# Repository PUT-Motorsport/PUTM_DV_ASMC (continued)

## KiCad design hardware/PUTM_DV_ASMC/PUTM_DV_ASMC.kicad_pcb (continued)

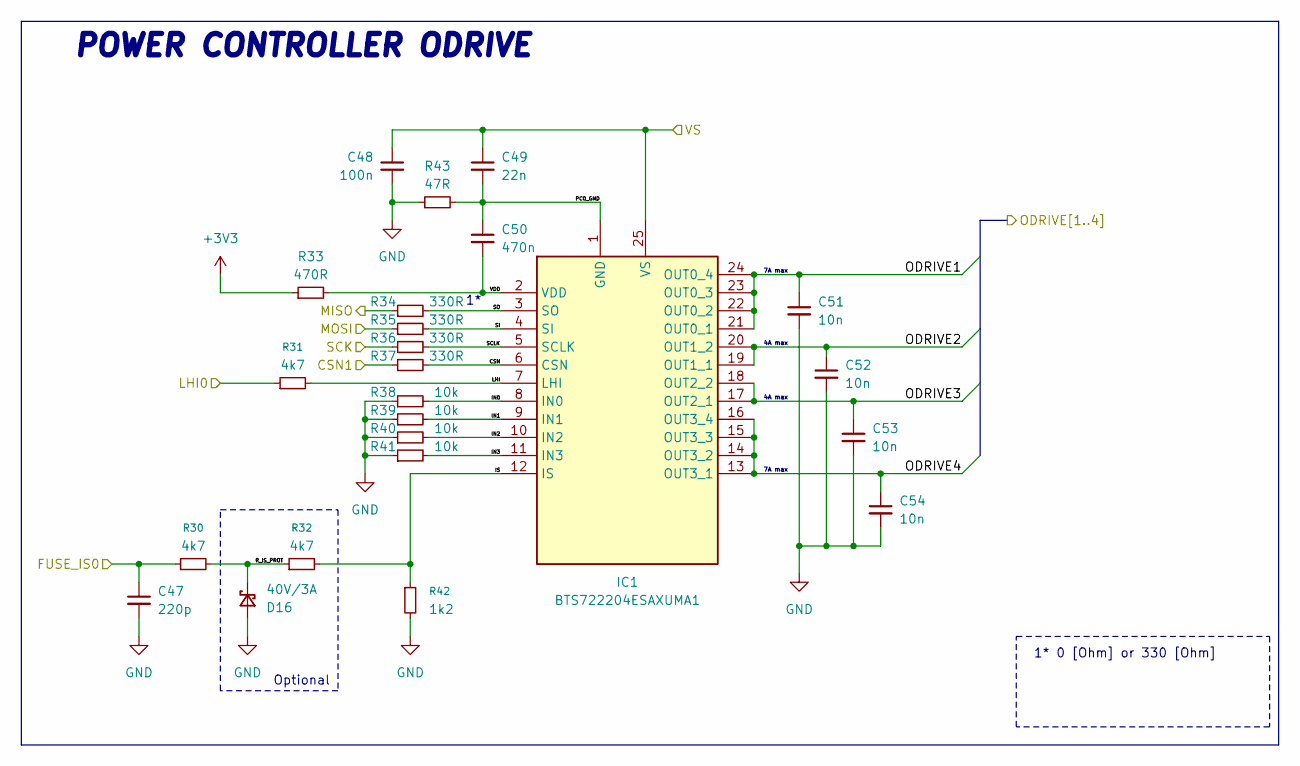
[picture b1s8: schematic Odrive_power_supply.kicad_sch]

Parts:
C47: 220p; C_0603_1608Metric_Pad1.08x0.95mm_HandSolder; Mouser Part Number 81-GCM1885C1H221JA6J
C48: 100n; C_0603_1608Metric_Pad1.08x0.95mm_HandSolder; Mouser Part Number 81-GCJ188R71H104KA2D
C49: 22n; C_0603_1608Metric_Pad1.08x0.95mm_HandSolder; Mouser Part Number GCE188R71H223KA01D
C50: 470n; C_0603_1608Metric_Pad1.08x0.95mm_HandSolder; Mouser Part Number 810-C1608X7R1H474K0E
C51, C52, C53, C54: 10n; C_0603_1608Metric_Pad1.08x0.95mm_HandSolder; Mouser Part Number 81-GCE188R71H103KA1D
D16: 40V/3A; D_SOD-123F; Mouser Part Number 637-SKL34
IC1: BTS722204ESAXUMA1; SOP65P600X115-25N; Mouser Part Number 726-BTS722204ESAXUMA
R30, R31, R32: 4k7; R_0603_1608Metric_Pad0.98x0.95mm_HandSolder; Mouser Part Number 71-CRCW0603-4.7K-E3
R33: 470R; R_0603_1608Metric_Pad0.98x0.95mm_HandSolder; Mouser Part Number 71-CRCW0603J-470-E3
R34, R35, R36, R37: 330R; R_0603_1608Metric_Pad0.98x0.95mm_HandSolder; Mouser Part Number 71-CRCW0603-330-E3
R38, R39, R40, R41: 10k; R_0603_1608Metric_Pad0.98x0.95mm_HandSolder; Mouser Part Number 71-CRCW060310K0FKEAH
R42: 1k2; R_0603_1608Metric_Pad0.98x0.95mm_HandSolder; Mouser Part Number 71-CRCW0603-1.2K-E3
R43: 47R; R_0603_1608Metric_Pad0.98x0.95mm_HandSolder; Mouser Part Number 71-RCS060347R0JNEA

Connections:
+3V3: R33.1; also elsewhere on the board
+BATT: C48.1, C49.1, IC1.25 (VS); also elsewhere on the board
/Connectors/ODRIVE4: C51.1, C52.1, C53.1, C54.1, IC1.13 (OUT3_1), IC1.14 (OUT3_2), IC1.15 (OUT3_3), IC1.16 (OUT3_4), IC1.17 (OUT2_1), IC1.18 (OUT2_2), IC1.19 (OUT1_1), IC1.20 (OUT1_2), IC1.21 (OUT0_1), IC1.22 (OUT0_2), IC1.23 (OUT0_3), IC1.24 (OUT0_4); also elsewhere on the board
/DV_power_supply/FUSE_IS0: C47.1, R30.1; also elsewhere on the board
/DV_power_supply/LHI0: R31.1; also elsewhere on the board
/DV_power_supply/Odrive_power_supply/CSN: IC1.6 (CSN), R37.2
/DV_power_supply/Odrive_power_supply/IN0: IC1.8 (IN0), R38.2
/DV_power_supply/Odrive_power_supply/IN1: IC1.9 (IN1), R39.2
/DV_power_supply/Odrive_power_supply/IN2: IC1.10 (IN2), R40.2
/DV_power_supply/Odrive_power_supply/IN3: IC1.11 (IN3), R41.2
/DV_power_supply/Odrive_power_supply/IS: IC1.12 (IS), R32.2, R42.1
/DV_power_supply/Odrive_power_supply/LHI: IC1.7 (LHI), R31.2
/DV_power_supply/Odrive_power_supply/PC0_GND: C49.2, C50.1, IC1.1 (GND), R43.2
/DV_power_supply/Odrive_power_supply/R_IS_PROT: D16.1 (K), R30.2, R32.1
/DV_power_supply/Odrive_power_supply/SCLK: IC1.5 (SCLK), R36.2
/DV_power_supply/Odrive_power_supply/SI: IC1.4 (SI), R35.2
/DV_power_supply/Odrive_power_supply/SO: IC1.3 (SO), R34.2
/DV_power_supply/Odrive_power_supply/VDD: C50.2, IC1.2 (VDD), R33.2
/DV_power_supply/SPI1.CSN1: R37.1; also elsewhere on the board
/DV_power_supply/SPI1.MISO: R34.1; also elsewhere on the board
/DV_power_supply/SPI1.MOSI: R35.1; also elsewhere on the board
/DV_power_supply/SPI1.SCK: R36.1; also elsewhere on the board
GND: C47.2, C48.2, C51.2, C52.2, C53.2, C54.2, D16.2 (A), R38.1, R39.1, R40.1, R41.1, R42.2, R43.1; also elsewhere on the board

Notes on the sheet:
4A max
Optional
1* 0 [Ohm] or 330 [Ohm]
POWER CONTROLLER ODRIVE
7A max

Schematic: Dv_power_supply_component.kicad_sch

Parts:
C55: 220p; C_0603_1608Metric_Pad1.08x0.95mm_HandSolder; Mouser Part Number 81-GCM1885C1H221JA6J
C56: 100n; C_0603_1608Metric_Pad1.08x0.95mm_HandSolder; Mouser Part Number 81-GCJ188R71H104KA2D
C57: 22n; C_0603_1608Metric_Pad1.08x0.95mm_HandSolder; Mouser Part Number GCE188R71H223KA01D
C58: 470n; C_0603_1608Metric_Pad1.08x0.95mm_HandSolder; Mouser Part Number 810-C1608X7R1H474K0E
C59, C60, C61, C62: 10n; C_0603_1608Metric_Pad1.08x0.95mm_HandSolder; Mouser Part Number 81-GCE188R71H103KA1D
D17: 40V/3A; D_SOD-123F; Mouser Part Number 637-SKL34
IC2: BTS722204ESAXUMA1; SOP65P600X115-25N; Mouser Part Number 726-BTS722204ESAXUMA
R44, R45, R46: 4k7; R_0603_1608Metric_Pad0.98x0.95mm_HandSolder; Mouser Part Number 71-CRCW0603-4.7K-E3
R47: 470R; R_0603_1608Metric_Pad0.98x0.95mm_HandSolder; Mouser Part Number 71-CRCW0603J-470-E3
R48, R49, R50, R51: 330R; R_0603_1608Metric_Pad0.98x0.95mm_HandSolder; Mouser Part Number 71-CRCW0603-330-E3
R52, R53, R54, R55: 10k; R_0603_1608Metric_Pad0.98x0.95mm_HandSolder; Mouser Part Number 71-CRCW060310K0FKEAH
R56: 1k2; R_0603_1608Metric_Pad0.98x0.95mm_HandSolder; Mouser Part Number 71-CRCW0603-1.2K-E3
R57: 47R; R_0603_1608Metric_Pad0.98x0.95mm_HandSolder; Mouser Part Number 71-RCS060347R0JNEA

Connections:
+3V3: R47.1; also elsewhere on the board
+BATT: C56.1, C57.1, IC2.25 (VS); also elsewhere on the board
/Connectors/OUT_ASSI: C60.1, IC2.19 (OUT1_1), IC2.20 (OUT1_2); also elsewhere on the board
/Connectors/OUT_EBS: C61.1, IC2.17 (OUT2_1), IC2.18 (OUT2_2); also elsewhere on the board
/Connectors/OUT_LIDAR: C59.1, IC2.21 (OUT0_1), IC2.22 (OUT0_2), IC2.23 (OUT0_3), IC2.24 (OUT0_4); also elsewhere on the board
/Connectors/OUT_RES: C62.1, IC2.13 (OUT3_1), IC2.14 (OUT3_2), IC2.15 (OUT3_3), IC2.16 (OUT3_4); also elsewhere on the board
/DV_power_supply/Dv_power_supply_component/CSN: IC2.6 (CSN), R51.2
/DV_power_supply/Dv_power_supply_component/IN0: IC2.8 (IN0), R52.2
/DV_power_supply/Dv_power_supply_component/IN1: IC2.9 (IN1), R53.2
/DV_power_supply/Dv_power_supply_component/IN2: IC2.10 (IN2), R54.2
/DV_power_supply/Dv_power_supply_component/IN3: IC2.11 (IN3), R55.2
/DV_power_supply/Dv_power_supply_component/IS: IC2.12 (IS), R46.2, R56.1
/DV_power_supply/Dv_power_supply_component/LHI: IC2.7 (LHI), R45.2
/DV_power_supply/Dv_power_supply_component/PC0_GND: C57.2, C58.1, IC2.1 (GND), R57.2
/DV_power_supply/Dv_power_supply_component/R_IS_PROT: D17.1 (K), R44.2, R46.1
/DV_power_supply/Dv_power_supply_component/SCLK: IC2.5 (SCLK), R50.2
/DV_power_supply/Dv_power_supply_component/SI: IC2.4 (SI), R49.2
/DV_power_supply/Dv_power_supply_component/SO: IC2.3 (SO), R48.2
/DV_power_supply/Dv_power_supply_component/VDD: C58.2, IC2.2 (VDD), R47.2
/DV_power_supply/FUSE_IS1: C55.1, R44.1; also elsewhere on the board
/DV_power_supply/LHI1: R45.1; also elsewhere on the board
/DV_power_supply/SPI1.CSN2: R51.1; also elsewhere on the board
/DV_power_supply/SPI1.MISO: R48.1; also elsewhere on the board
/DV_power_supply/SPI1.MOSI: R49.1; also elsewhere on the board
/DV_power_supply/SPI1.SCK: R50.1; also elsewhere on the board
GND: C55.2, C56.2, C59.2, C60.2, C61.2, C62.2, D17.2 (A), R52.1, R53.1, R54.1, R55.1, R56.2, R57.1; also elsewhere on the board

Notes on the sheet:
POWER CONTROLLER DV COMPONENTS
1* 0 [Ohm] or 330 [Ohm]
7A max
Optional
4A max

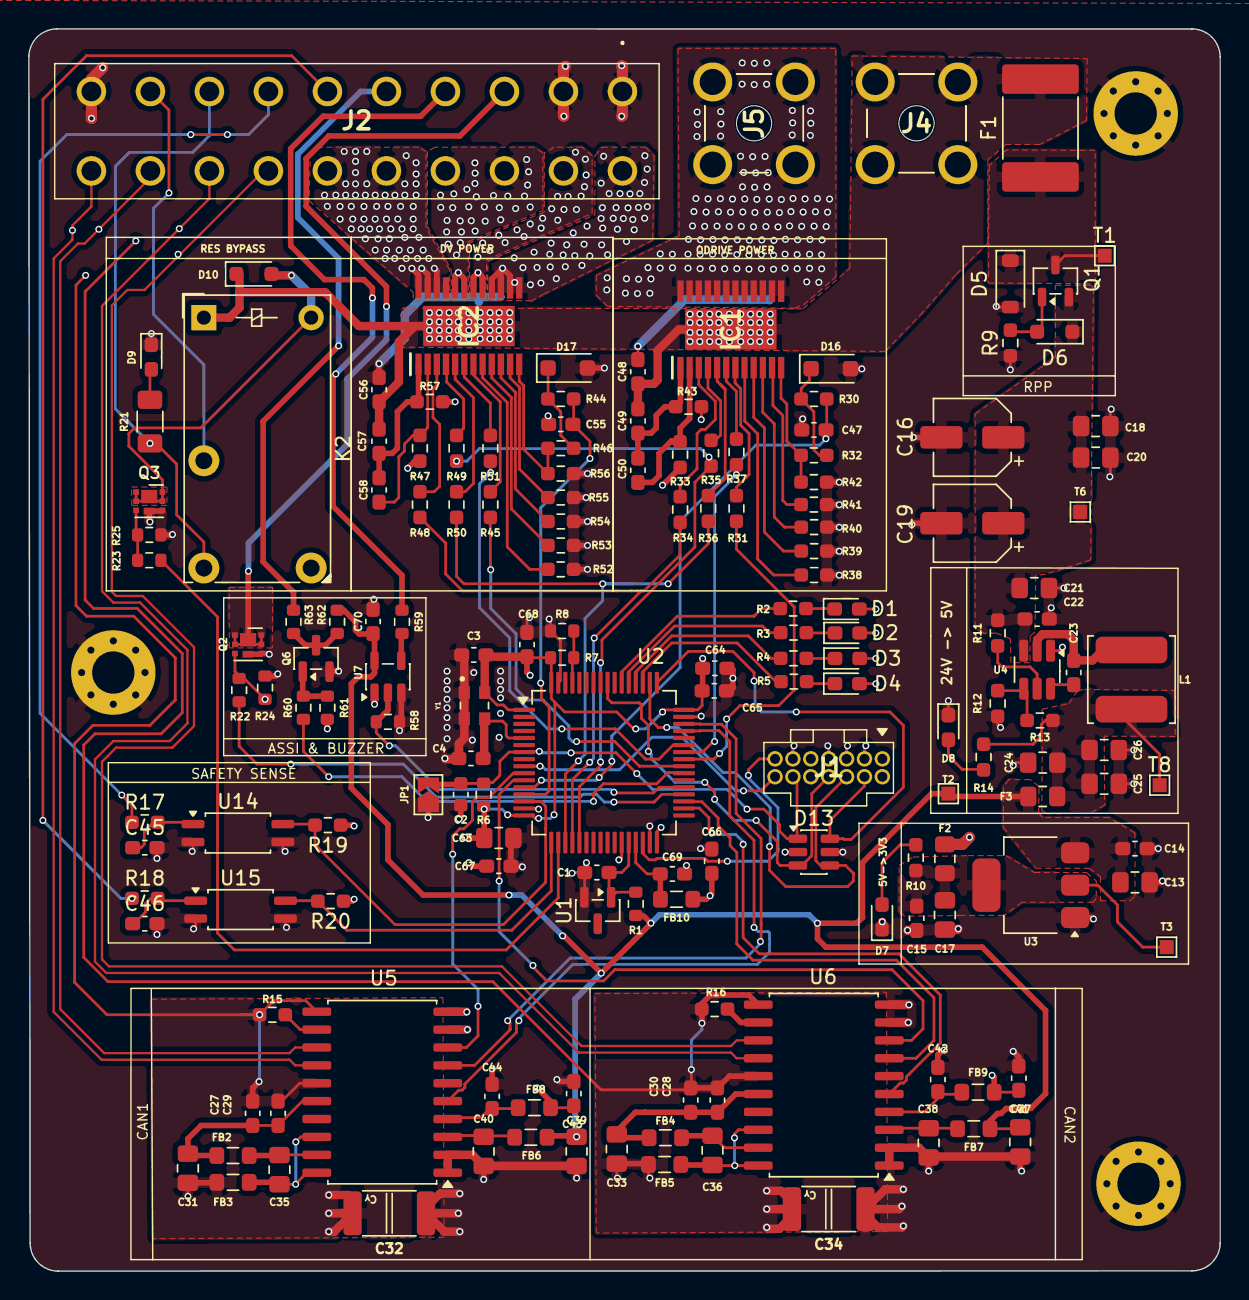
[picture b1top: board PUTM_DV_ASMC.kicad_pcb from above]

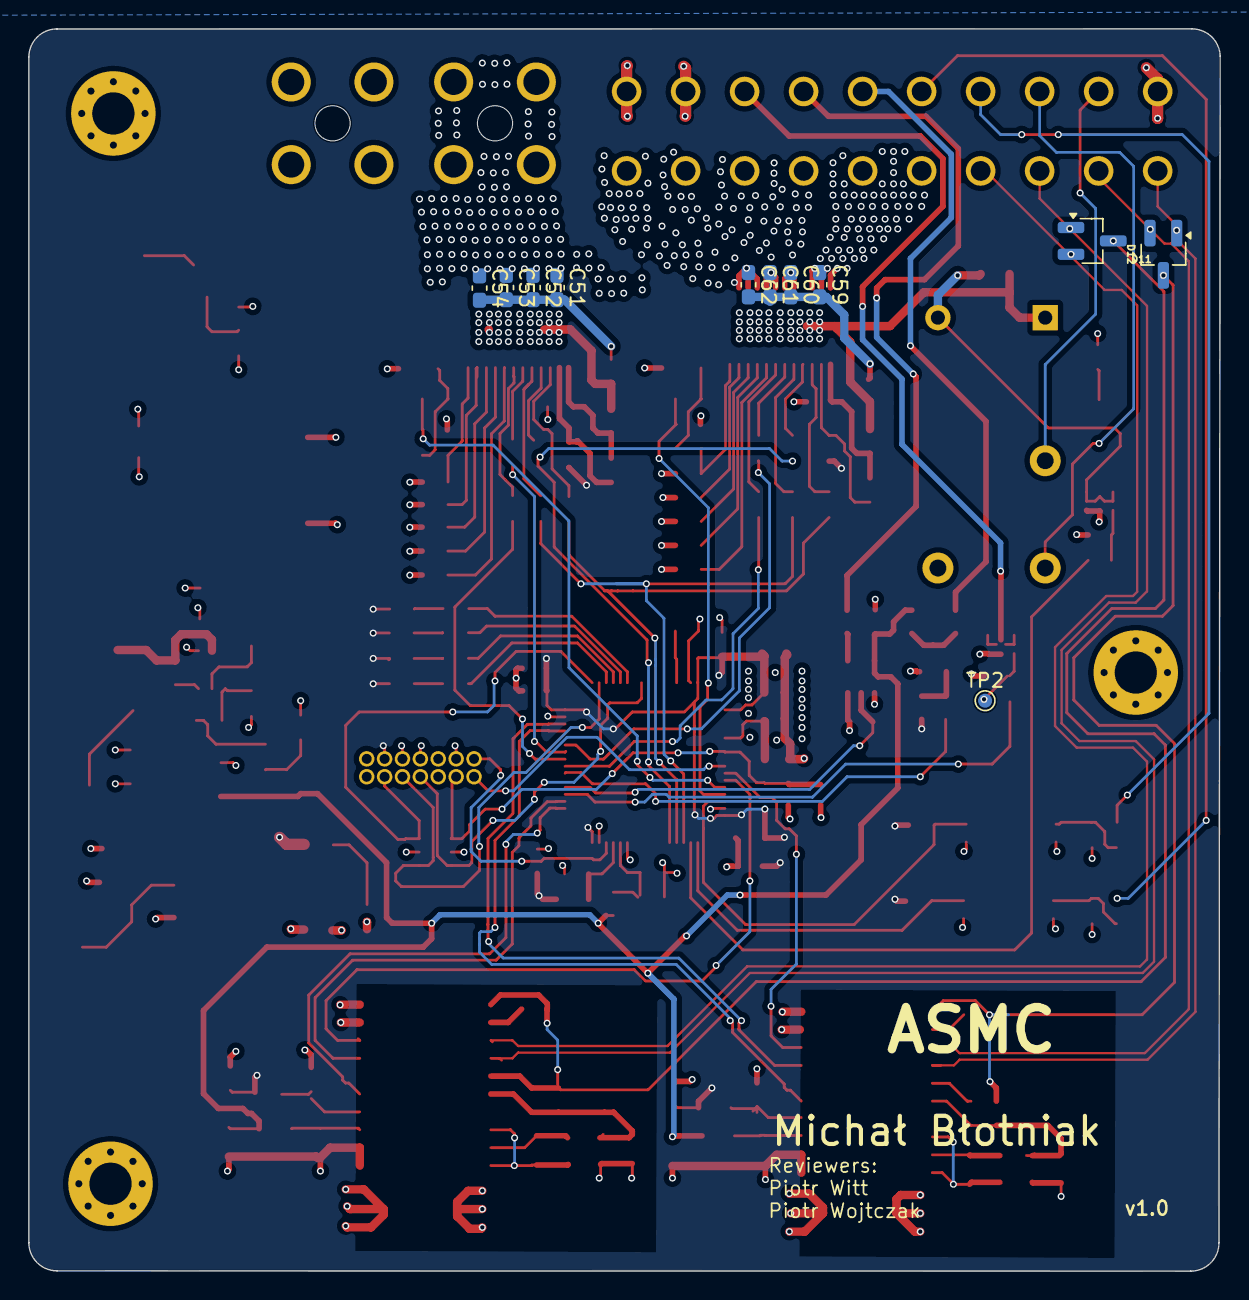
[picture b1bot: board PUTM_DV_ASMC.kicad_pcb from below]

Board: 4 copper layers, 84.6 x 88.2 mm, 177 parts (11 on the bottom side), 119 nets.

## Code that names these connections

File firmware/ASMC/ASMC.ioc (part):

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Mcu.Name=STM32G484RETx
Mcu.Package=LQFP64
Mcu.UserName=STM32G484RETx
PA0.GPIOParameters=GPIO_Label
PA0.GPIO_Label=FUSE_IS0
PA0.Signal=ADC1_IN1
PA1.GPIOParameters=GPIO_Label
PA1.GPIO_Label=FUSE_IS1
PA1.Signal=ADC2_IN2
PA11.Mode=FDCAN_Activate
PA11.Signal=FDCAN1_RX
PA12.Mode=FDCAN_Activate
PA12.Signal=FDCAN1_TX
PA13.Mode=Serial_Wire
PA13.Signal=SYS_JTMS-SWDIO
PA14.Mode=Serial_Wire
PA14.Signal=SYS_JTCK-SWCLK
PA15.GPIOParameters=GPIO_Label
PA15.GPIO_Label=DEBUG_LED_4
PA15.Signal=GPIO_Output
PA2.GPIOParameters=GPIO_Label
PA2.GPIO_Label=AS_SENSE
PA2.Signal=GPIO_Input
PA3.GPIOParameters=GPIO_Label
PA3.GPIO_Label=RES_SENSE
PA3.Signal=GPIO_Input
PA4.GPIOParameters=GPIO_Label
PA4.GPIO_Label=RES_BYPASS
PA4.Signal=GPIO_Output
PA5.Mode=Full_Duplex_Master
PA5.Signal=SPI1_SCK
PA6.Mode=Full_Duplex_Master
PA6.Signal=SPI1_MISO
PA7.Mode=Full_Duplex_Master
PA7.Signal=SPI1_MOSI
PA8.GPIOParameters=GPIO_Label
PA8.GPIO_Label=SPI1_CSN1
PA8.Signal=GPIO_Output
PA9.GPIOParameters=GPIO_Label
PA9.GPIO_Label=SPI1_CSN2
PA9.Signal=GPIO_Output
PB0.Mode=IN12-Single-Ended
PB0.Signal=ADC3_IN12
PB1.Signal=GPIO_Output
PB10.Mode=Asynchronous
PB10.Signal=LPUART1_RX
PB12.Mode=FDCAN_Activate
PB12.Signal=FDCAN2_RX
PB13.Mode=FDCAN_Activate
PB13.Signal=FDCAN2_TX
PB14.GPIOParameters=GPIO_Label
PB14.GPIO_Label=BUZZER
PB14.Signal=GPIO_Input
PB15.GPIOParameters=GPIO_Label
PB15.GPIO_Label=ASSI_SIG1
PB15.Signal=SPI2_MOSI
PC1.Mode=Asynchronous
PC1.Signal=LPUART1_TX
PC10.GPIOParameters=GPIO_Label
PC10.GPIO_Label=DEBUG_LED_3
PC10.Signal=GPIO_Output
PC11.GPIOParameters=GPIO_Label
PC11.GPIO_Label=DEBUG_LED_2
PC11.Signal=GPIO_Output
PC12.GPIOParameters=GPIO_Label
PC12.GPIO_Label=DEBUG_LED_1
PC12.Signal=GPIO_Output
PC2.GPIOParameters=GPIO_Label
PC2.GPIO_Label=STBY_CAN_1
PC2.Signal=GPIO_Output
PC3.GPIOParameters=GPIO_Label
PC3.GPIO_Label=STBY_CAN_2
PC3.Signal=GPIO_Output
PC7.GPIOParameters=GPIO_Label
PC7.GPIO_Label=ASSI_SIG2
PC7.Signal=GPIO_Output
PC8.GPIOParameters=GPIO_Label
PC8.GPIO_Label=LHI1
PC8.Signal=GPIO_Output
PC9.GPIOParameters=GPIO_Label
PC9.GPIO_Label=LHI0
PC9.Signal=GPIO_Output
PF0-OSC_IN.Mode=HSE-External-Oscillator
PF0-OSC_IN.Signal=RCC_OSC_IN
PF1-OSC_OUT.Mode=HSE-External-Oscillator
PF1-OSC_OUT.Signal=RCC_OSC_OUT
RCC.HSE_VALUE=8000000
RCC.SYSCLKFreq_VALUE=160000000
RCC.SYSCLKSource=RCC_SYSCLKSOURCE_PLLCLK
board=custom

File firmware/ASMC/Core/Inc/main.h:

/* USER CODE BEGIN Header */
/**
  ******************************************************************************
  * @file           : main.h
  * @brief          : Header for main.c file.
  *                   This file contains the common defines of the application.
  ******************************************************************************
  * @attention
  *
  * Copyright (c) 2026 STMicroelectronics.
  * All rights reserved.
  *
  * This software is licensed under terms that can be found in the LICENSE file
  * in the root directory of this software component.
  * If no LICENSE file comes with this software, it is provided AS-IS.
  *
  ******************************************************************************
  */
/* USER CODE END Header */

/* Define to prevent recursive inclusion -------------------------------------*/
#ifndef __MAIN_H
#define __MAIN_H

#ifdef __cplusplus
extern "C" {
#endif

/* Includes ------------------------------------------------------------------*/
#include "stm32g4xx_hal.h"

/* Private includes ----------------------------------------------------------*/
/* USER CODE BEGIN Includes */

/* USER CODE END Includes */

/* Exported types ------------------------------------------------------------*/
/* USER CODE BEGIN ET */

/* USER CODE END ET */

/* Exported constants --------------------------------------------------------*/
/* USER CODE BEGIN EC */

/* USER CODE END EC */

/* Exported macro ------------------------------------------------------------*/
/* USER CODE BEGIN EM */

/* USER CODE END EM */

/* Exported functions prototypes ---------------------------------------------*/
void Error_Handler(void);

/* USER CODE BEGIN EFP */

/* USER CODE END EFP */

/* Private defines -----------------------------------------------------------*/
#define STBY_CAN_1_Pin GPIO_PIN_2
#define STBY_CAN_1_GPIO_Port GPIOC
#define STBY_CAN_2_Pin GPIO_PIN_3
#define STBY_CAN_2_GPIO_Port GPIOC
#define AS_SENSE_Pin GPIO_PIN_2
#define AS_SENSE_GPIO_Port GPIOA
#define RES_SENSE_Pin GPIO_PIN_3
#define RES_SENSE_GPIO_Port GPIOA
#define RES_BYPASS_Pin GPIO_PIN_4
#define RES_BYPASS_GPIO_Port GPIOA
#define SPI1_NSS_Pin GPIO_PIN_8
#define SPI1_NSS_GPIO_Port GPIOA
#define DEBUG_LED_1_Pin GPIO_PIN_4
#define DEBUG_LED_1_GPIO_Port GPIOB
#define DEBUG_LED_2_Pin GPIO_PIN_5
#define DEBUG_LED_2_GPIO_Port GPIOB
#define DEBUG_LED_3_Pin GPIO_PIN_6
#define DEBUG_LED_3_GPIO_Port GPIOB
#define DEBUG_LED_4_Pin GPIO_PIN_7
#define DEBUG_LED_4_GPIO_Port GPIOB
#define ASSI_DI_Pin GPIO_PIN_8
#define ASSI_DI_GPIO_Port GPIOB
#define ASSI_DO_Pin GPIO_PIN_9
#define ASSI_DO_GPIO_Port GPIOB

/* USER CODE BEGIN Private defines */

/* USER CODE END Private defines */

#ifdef __cplusplus
}
#endif

#endif /* __MAIN_H */

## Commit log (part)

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2026-03-26 update gitignore file
2026-03-26 make mcu section
2026-04-19 assi section
2026-04-19 io section
2026-04-19 can section
2026-04-19 uC section work
2026-04-24 schematics without main connector
2026-04-24 add cubemx config pins
2026-05-28 done schematic v1
2026-05-28 schematic without error
2026-05-28 tylko dwa bledy z can - schemat na wykonczeniu
2026-05-28 poprawki footprint
2026-05-29 work on power layout
2026-05-29 make function section
2026-05-29 update pins mcu
2026-05-30 make zones
2026-05-30 work on supply and zones
2026-05-30 work work work
2026-05-30 can layout
2026-05-31 update pcb after review
2026-06-01 pcb woithout iso gnd
2026-06-01 pcb 99.5proc
2026-06-01 pcb 100%
2026-06-01 edit settings dla marudy PL
